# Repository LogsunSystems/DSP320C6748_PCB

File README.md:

### DSP320C6748 DSP DVK Board

The DVK board is based on the DSP chip from *Texas Instruments* DSP chip **DSP320C6748**. 

## Introduction
**DSP320C6748 DVK** is a scalable evaluation platform designed for high-performance applications requiring *real-time signal processing* and *embedded analytics*.

## Specifications
- **Processor:-** TSM320C6748 DSP with fixed and floating point core running at performance levels up to 456MHz
- **RAM:-**
- **Flash:-** 2Gbit, 16-bit Bus, Parallel Flash memory
- **Audio Coded:-**
- **Video Coded:-**
- **Connectivity:-**
- **Interfaces:-** 
    - Camera Connector
    - LCD Connector
    - RCA Video IN
    - Audio Line IN
    - MIC IN
    - Speaker IN (Mono)

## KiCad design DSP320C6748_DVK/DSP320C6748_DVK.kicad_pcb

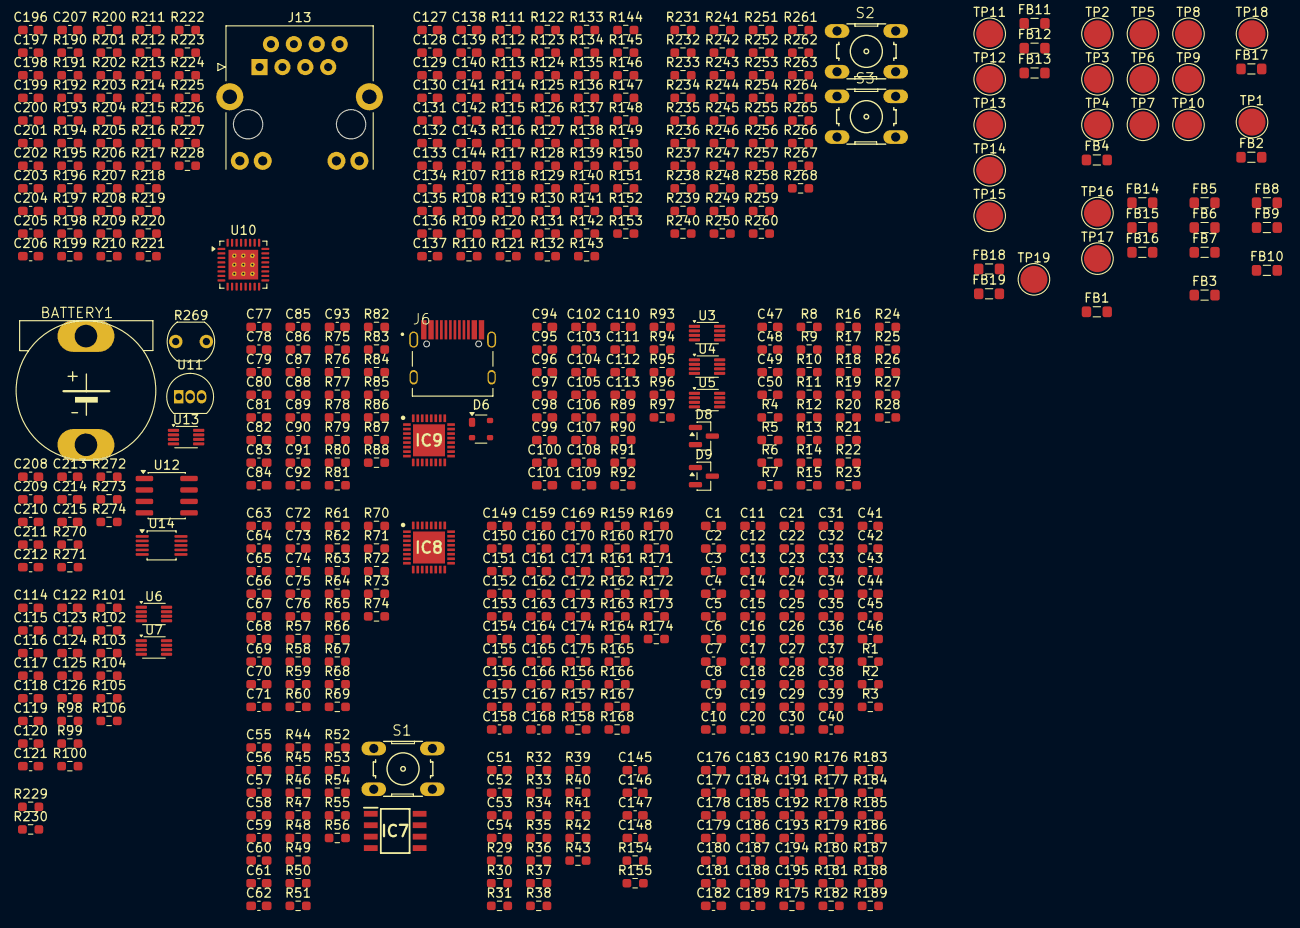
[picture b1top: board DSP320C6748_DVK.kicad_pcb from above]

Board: 8 copper layers, 549 parts (0 on the bottom side), 159 nets, no tracks yet.

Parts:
BATTERY1: LGS-KC-LEADED
C1, C2: 0.22uF/6.3V X5R; C_0603_1608Metric_Pad1.08x0.95mm_HandSolder
C3, C4, C5, C6, C7, C8, C9, C10, C11, C12, C13, C14, C15, C16, C17, C18, C19, C20, C21, C22, C23, C25, C26, C27, C28, C29, C30, C31, C32, C33, C34, C35, C36, C37, C39, C40, C41, C43, C47, C57, C58, C61, C62, C77, C78, C79, C81, C82, C91, C93, C94, C95, C96, C97, C98, C99, C102, C106, C112, C114, C115, C116, C117, C118, C119, C120, C121, C122, C123, C124, C125, C126, C127, C128, C130, C132, C134, C138, C139, C142, C145, C146, C149, C150, C151, C152, C153, C155, C156, C157, C158, C159, C160, C161, C162, C163, C164, C165, C166, C167, C168, C169, C170, C171, C172, C175, C176, C178, C180, C182, C185, C186, C187, C189, C192, C193, C195, C196, C202, C204, C210, C211, C212, C213, C215: 0.1uF/16V/X7R; C_0603_1608Metric_Pad1.08x0.95mm_HandSolder
C24, C38, C42, C44, C45, C46, C49, C55, C56, C59, C60, C63, C64, C65, C66, C67, C68, C69, C73, C75, C80, C83, C87, C88, C92, C113, C129, C137, C143, C188, C190, C191, C194, C206, C214: 10uF/10V/X5R; C_0603_1608Metric_Pad1.08x0.95mm_HandSolder
C48, C50, C173, C174: 22pF,50V NPO; C_0603_1608Metric_Pad1.08x0.95mm_HandSolder
C51, C52, C53, C54, C84, C85, C131, C133, C135, C136, C140, C141, C144, C147: 0.01uF/16V/X7R; C_0603_1608Metric_Pad1.08x0.95mm_HandSolder
C70, C71, C109, C148, C197: 1uF/10V/X5R; C_0603_1608Metric_Pad1.08x0.95mm_HandSolder
C72, C74, C76: 2.2uF/6.3V/X5R; C_0603_1608Metric_Pad1.08x0.95mm_HandSolder
C86: 10pF,50V NPO; C_0603_1608Metric_Pad1.08x0.95mm_HandSolder
C89: 4.7uF; C_0603_1608Metric_Pad1.08x0.95mm_HandSolder
C90: 0.1uF; C_0603_1608Metric_Pad1.08x0.95mm_HandSolder
C100, C104, C105: 100pF/25V; C_0603_1608Metric_Pad1.08x0.95mm_HandSolder
C101, C107, C108: 33pF/50V; C_0603_1608Metric_Pad1.08x0.95mm_HandSolder
C103, C110, C111: 270pF/50V; C_0603_1608Metric_Pad1.08x0.95mm_HandSolder
C154: 330pF/100V/X7R; C_0603_1608Metric_Pad1.08x0.95mm_HandSolder
C177: 1uF/16V/X7R; C_0603_1608Metric_Pad1.08x0.95mm_HandSolder
C179, C181: 220pF/50V X7R; C_0603_1608Metric_Pad1.08x0.95mm_HandSolder
C183, C184: 0.47uF/16V/X5R; C_0603_1608Metric_Pad1.08x0.95mm_HandSolder
C198, C199: 33pF,50V NPO; C_0603_1608Metric_Pad1.08x0.95mm_HandSolder
C200, C201, C203, C205: 10pF; C_0603_1608Metric_Pad1.08x0.95mm_HandSolder
C207: 0.022uF,50V; C_0603_1608Metric_Pad1.08x0.95mm_HandSolder
C208, C209: 12.5pF; C_0603_1608Metric_Pad1.08x0.95mm_HandSolder
D6: SP0503BAHT; SOT-143
D8, D9: BAV99; SOT-23
FB1, FB2, FB3, FB4, FB5, FB6, FB7, FB8, FB9, FB10, FB11, FB12, FB13, FB14, FB15, FB16, FB17, FB18, FB19: MMZ2012S121A; L_0805_2012Metric_Pad1.05x1.20mm_HandSolder
IC7: TPS3707-33DR; SOIC127P600X175-8N
IC8: TPS650250RHBR; QFN50P500X500X100-33N-D
IC9: CDCM61001RHBT; QFN50P500X500X100-33N-D
J6: USB_Type_C; LGS-KC-VALCON_CSP-USC16-TR
J13: RJ45_Halo_HFJ11-x2450E-LxxRL; RJ45_HALO_HFJ11-x2450E-LxxRL_Horizontal
R1: 0R, 5%, 1/10W; R_0603_1608Metric_Pad0.98x0.95mm_HandSolder
R2: 0R; R_0603_1608Metric_Pad0.98x0.95mm_HandSolder
R3: 49.9R, 1%, 1/16W; R_0603_1608Metric_Pad0.98x0.95mm_HandSolder
R4, R21, R36, R37, R38, R39: 100R,1%,1/16W; R_0603_1608Metric_Pad0.98x0.95mm_HandSolder
R5, R6, R11, R12, R22, R23, R24, R32, R33, R34, R35, R45, R82, R83, R91, R92, R93, R94, R95, R96, R97, R161, R261, R262: 10K,1%,1/16W; R_0603_1608Metric_Pad0.98x0.95mm_HandSolder
R7, R8, R9, R10, R13, R14, R16, R44, R49, R51, R53, R55, R56, R67, R70, R71, R72, R75, R76, R77, R78, R79, R80, R81, R98, R100, R101, R103, R105, R134, R154, R155, R157, R158, R162, R163, R164, R165, R166, R167, R168, R169, R170, R171, R172, R183, R192, R194, R204, R205, R207, R209, R210, R212, R213, R272, R273, R274: 4.7K,5%,1/16W; R_0603_1608Metric_Pad0.98x0.95mm_HandSolder
R15, R17, R89, R90: 2.2K,5%; R_0603_1608Metric_Pad0.98x0.95mm_HandSolder
R18, R19, R20, R109, R110, R119, R120, R130, R131, R132, R135, R136, R137, R138, R139: 22R,1%,1/16W; R_0603_1608Metric_Pad0.98x0.95mm_HandSolder
R25: 180R,1%; R_0603_1608Metric_Pad0.98x0.95mm_HandSolder
R26: 120R,1%; R_0603_1608Metric_Pad0.98x0.95mm_HandSolder
R27, R28, R31, R69, R74, R159, R175, R176, R214, R217, R218, R219, R220, R221, R222, R229, R230: 0R,5%,1/10W; R_0603_1608Metric_Pad0.98x0.95mm_HandSolder
R29, R30, R184: 33R,5%,1/16W; R_0603_1608Metric_Pad0.98x0.95mm_HandSolder
R40, R41, R265, R266: 100K,5%,1/16W; R_0603_1608Metric_Pad0.98x0.95mm_HandSolder
R42, R43, R227, R228, R267, R268: 330R,5%,1/16W; R_0603_1608Metric_Pad0.98x0.95mm_HandSolder
R46, R47: 5.1K; R_0603_1608Metric_Pad0.98x0.95mm_HandSolder
R48: 510R,5%,1/16W; R_0603_1608Metric_Pad0.98x0.95mm_HandSolder
R50, R231, R232, R233, R234, R239, R240, R241, R242, R243, R244, R253, R254, R255, R256, R257, R258, R259, R260, R263, R264: 1K.1%,1/16W; R_0603_1608Metric_Pad0.98x0.95mm_HandSolder
R52: 1K; R_0603_1608Metric_Pad0.98x0.95mm_HandSolder
R54, R107, R124: 1K,1%,1/16W; R_0603_1608Metric_Pad0.98x0.95mm_HandSolder
R57: 576K,1%,1/10W; R_0603_1608Metric_Pad0.98x0.95mm_HandSolder
R58: 60.4K,1%,1/16W; R_0603_1608Metric_Pad0.98x0.95mm_HandSolder
R59, R60, R61: 0.05R,1%,Sense; R_0603_1608Metric_Pad0.98x0.95mm_HandSolder
R62: 499K,1%,1/16W; R_0603_1608Metric_Pad0.98x0.95mm_HandSolder
R63: 300K,1%,1/16W; R_0603_1608Metric_Pad0.98x0.95mm_HandSolder
R64: 200K,1%,1/16W; R_0603_1608Metric_Pad0.98x0.95mm_HandSolder
R65: 160K,1%,1/10W; R_0603_1608Metric_Pad0.98x0.95mm_HandSolder
R66: 1R,1%,1/16W; R_0603_1608Metric_Pad0.98x0.95mm_HandSolder
R68: 1.4K,1%,1/16W; R_0603_1608Metric_Pad0.98x0.95mm_HandSolder
R73: 5.6K,1%,1/16W; R_0603_1608Metric_Pad0.98x0.95mm_HandSolder
R84: 22.1K,1%,1/4W; R_0603_1608Metric_Pad0.98x0.95mm_HandSolder
R85: 47.5K,1%,1/4W; R_0603_1608Metric_Pad0.98x0.95mm_HandSolder
R86: 1K,1%,1/4W; R_0603_1608Metric_Pad0.98x0.95mm_HandSolder
R87, R88, R173: 1K,5%,1/16W; R_0603_1608Metric_Pad0.98x0.95mm_HandSolder
R99: 3.4K,1%,1/16W; R_0603_1608Metric_Pad0.98x0.95mm_HandSolder
R102, R104, R106, R156: 75R,5%,1/16W; R_0603_1608Metric_Pad0.98x0.95mm_HandSolder
R108, R111, R112, R113, R114, R115, R116, R117, R118, R121, R122, R123, R125, R126, R127, R128, R129, R133, R140, R141, R142, R143, R144, R145, R146, R147, R148, R149, R150, R151, R152, R153, R208, R225: 10R,1%,1/16W; R_0603_1608Metric_Pad0.98x0.95mm_HandSolder
R160: 100K,5%; R_0603_1608Metric_Pad0.98x0.95mm_HandSolder
R174: 20K,5%,1/16W; R_0603_1608Metric_Pad0.98x0.95mm_HandSolder
R177, R180, R181, R182, R188, R189: 2K,1%,1,16W; R_0603_1608Metric_Pad0.98x0.95mm_HandSolder
R178, R179: 5.6K,1%; R_0603_1608Metric_Pad0.98x0.95mm_HandSolder
R185, R186: 20K,1%,1/16W; R_0603_1608Metric_Pad0.98x0.95mm_HandSolder
R187: 20K,5%; R_0603_1608Metric_Pad0.98x0.95mm_HandSolder
R190, R191: 1.5K,1%,1,16W; R_0603_1608Metric_Pad0.98x0.95mm_HandSolder
R193, R195, R196, R197, R198, R199, R200, R201, R202, R203: 100R,1%,1,16W; R_0603_1608Metric_Pad0.98x0.95mm_HandSolder
R206: 1M,1%,1/16%; R_0603_1608Metric_Pad0.98x0.95mm_HandSolder
R211: 12.1K,1%,1,16W; R_0603_1608Metric_Pad0.98x0.95mm_HandSolder
R215, R216, R223, R224: 49.9R,1%,1/16W; R_0603_1608Metric_Pad0.98x0.95mm_HandSolder
R226: 0R,5%,1210; R_0603_1608Metric_Pad0.98x0.95mm_HandSolder
R235, R236, R237, R238: 10K.1%,1/16W; R_0603_1608Metric_Pad0.98x0.95mm_HandSolder
R245, R246, R247, R248, R249, R250, R251, R252: 5.6K.1%,1/16W; R_0603_1608Metric_Pad0.98x0.95mm_HandSolder
R269: LDR07; R_LDR_5.1x4.3mm_P3.4mm_Vertical
R270: 10K; R_0603_1608Metric_Pad0.98x0.95mm_HandSolder
R271: 45K; R_0603_1608Metric_Pad0.98x0.95mm_HandSolder
S1, S2, S3: Tact_SW; LGS-KC-B3F-10XX
TP1, TP2, TP3, TP4, TP5, TP6, TP7, TP8, TP9, TP10, TP11, TP12, TP13, TP14, TP15, TP16, TP17, TP18, TP19: TestPoint_Alt; TestPoint_Pad_D3.0mm
U3, U6, U13: TXS0102DCU; VSSOP-8_2.3x2mm_P0.5mm
U4, U5, U7: SN74LVC2T45DCUR; VSSOP-8_2.3x2mm_P0.5mm
U10: LAN8710A; QFN-32-1EP_5x5mm_P0.5mm_EP3.3x3.3mm_ThermalVias
U11: LM35-LP; TO-92_Inline
U12: DS1307Z+; SOIC-8_3.9x4.9mm_P1.27mm
U14: ADS1115IDGS; TSSOP-10_3x3mm_P0.5mm

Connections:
5VD_IN: C59.1, C60.1, C61.1, R44.2, TP7.1 (1_1)
5V_{IN}: C55.1, C56.1, C57.1, R45.1
+1V3D: C8.1, C12.1, C16.1, C19.1, C23.1, C27.1, C30.1, C33.1, C37.1, C40.1, C44.1, C65.1, C68.1, R1.1, R2.1, R50.1, R61.1, TP5.1 (1_1)
+1V8D_Audio: C176.2, C177.2, FB14.1
+3V3ADAC: C106.1, C109.2, C114.1, FB8.2
+3V3A_ADC: C211.2, C213.2, C214.1, FB18.1, R269.1, R273.1, U11.1 (+V_{S}), U14.8 (VDD)
+3V3A_Audio: C192.2, C193.2, C194.1, FB16.1
+3V3A_Flash: C145.2, C146.2, C147.2, C148.2, FB10.2, R154.1, R155.1
+3V3A_LAN: C202.2, C204.2, C206.1, FB17.2, R215.2, R216.2, R223.2, R224.2, R225.1, U10.1 (VDD2A), U10.27 (VDD1A)
+3V3A_{SATA}: C77.1, C78.1, C79.1, C80.1, FB6.1, IC9.9 (VCC__VCO), IC9.16 (VCC__PLL2), IC9.18 (VCC__PLL1)
+3V3D_Audio: C180.2, C182.2, C185.2, C187.2, C188.1, FB15.1
/ADC_RTC/ADDR: R274.2, U14.1 (ADDR)
/ADC_RTC/ALERT/RDY: R273.2, U14.2 (ALERT/RDY)
/ADC_RTC/LDR: R269.2, R270.1
/ADC_RTC/SQW/OUT: R272.2, TP19.1 (1_1), U12.7 (SQW/OUT)
/ADC_RTC/VBAT: BATTERY1.P1 (+), U12.3 (VBAT)
/ADC_RTC/X1: C208.2, U12.1 (X1)
/ADC_RTC/X2: R271.2, U12.2 (X2)
/DSP-I/OSC_{IN}: R25.2, R26.1
/LAN_8710A/ACT_LED: R212.2, R227.1, U10.3 (LED1/~REGOFF)
/LAN_8710A/ENET_RXN: C203.1, J13.6 (RD-), R223.1, U10.30 (RXN)
/LAN_8710A/ENET_RXP: C205.1, J13.3 (RD+), R224.1, U10.31 (RXP)
/LAN_8710A/ENET_TXN: C200.1, J13.2 (TD-), R215.1, U10.28 (TXN)
/LAN_8710A/ENET_TXP: C201.1, J13.1 (TD+), R216.1, U10.29 (TXP)
/LAN_8710A/LINK_LED: J13.10, R213.2, U10.2 (LED2/~INTSEL)
/LAN_8710A/RXD2: R193.1, R210.1, U10.9 (RXD2/~RMIISEL)
/Power_Supply-I/~MR: IC7.1 (~MR), S1.1 (S), S1.2 (S1)
/Serial_SATA/CE: IC9.7 (CE), R83.1
/Serial_SATA/OD0: IC9.13 (OD0), R76.1
/Serial_SATA/OD1: IC9.14 (OD1), R79.1
/Serial_SATA/OD2: IC9.15 (OD2), R77.1
/Serial_SATA/OS0: IC9.11 (OS0), R75.1
/Serial_SATA/OS1: IC9.10 (OS1), R78.1
/Serial_SATA/OUTN: C85.1, IC9.5 (OUTN)
/Serial_SATA/OUTP: C84.1, IC9.6 (OUTP)
/Serial_SATA/PR0: IC9.25 (PR0), R81.1
/Serial_SATA/PR1: IC9.26 (PR1), R80.1
/Serial_SATA/REG_CAP1: C87.1, IC9.19 (REG_CAP1)
/Serial_SATA/REG_CAP2: C88.1, IC9.17 (REG_CAP2)
/Serial_SATA/USB_UART_DN: D6.3 (K), J6.A7 (DN1), J6.B7 (DN2)
/Serial_SATA/USB_UART_DP: D6.4 (K), J6.A6 (DP1), J6.B6 (DP2)
/Serial_SATA/USB_VBUS: C91.1, FB7.1, J6.A4 (VBUS_A), J6.A9 (VBUS_A), J6.B4 (VBUS_B), J6.B9 (VBUS_B)
/Serial_SATA/USB_VCC: C92.1, C93.1, D6.2 (K), FB7.2, R84.1
/Serial_SATA/VBUS: R84.2, R85.1
/Serial_SATA/VIO: C89.1, C90.1, R86.2
/Serial_SATA/XIN: C86.1, IC9.21 (XIN)
/Sound_Coded/Audio_Left: C191.2, R185.2
/Sound_Coded/Audio_Right: C190.2, R186.2
/Sound_Coded/MIC_BIAS: R177.2, R180.2
/Sound_Coded/MIC_DET: C184.2, R180.1
/Sound_Coded/SELECT: R188.1, R189.2
/Video_Decoder (page 12)/XTAL1: C173.1, R160.1
/Video_Decoder (page 12)/XTAL2: R159.2, R160.2
A18VDD_REF: C155.2, C158.2, FB12.2
ABPB: C100.1, C101.1, R106.1
AGND1: FB4.2, IC8.13 (AGND2), IC8.31 (AGND1), IC8.33 (EP)
AGY: C104.1, C107.1, R102.1
ARPR: C105.1, C108.1, R104.1
CH1_A33VDD: C166.2, C169.2, FB13.2
DDC_SCL: D9.3 (K), R90.2, U3.8 (B1)
DDC_SDA: D8.3 (K), R89.2, U3.1 (B2)
DEFDCDC1: C69.1, C70.1, C71.2, C73.1, C75.1, C96.2, C98.1, C210.1, D8.2 (A), D9.2 (A), IC8.4 (VINDCDC3), IC8.5 (VINDCDC1), IC8.9 (DEFDCDC1), IC8.15 (VINLDO), IC8.28 (VINDCDC2), R51.1, R52.1, R53.1, R55.1, R56.1, R66.1, R70.1, R71.1, R72.1, R73.1, R74.1, R89.1, R90.1, R267.1, R268.1, R272.1, TP3.1 (1_1), U3.7 (VCCB), U5.1 (VCCA), U12.8 (VCC), U13.3 (VCCA), U13.6 (OE)
DEFDCDC2: BATTERY1.P2 (-), C1.2, C2.2, C3.2, C4.2, C5.2, C6.2, C7.2, C8.2, C9.2, C10.2, C11.2, C12.2, C13.2, C14.2, C15.2, C16.2, C17.2, C18.2, C19.2, C20.2, C21.2, C22.2, C23.2, C24.2, C25.2, C26.2, C27.2, C28.2, C29.2, C30.2, C31.2, C32.2, C33.2, C34.2, C35.2, C36.2, C37.2, C38.2, C39.2, C40.2, C41.2, C42.2, C43.2, C44.2, C45.2, C46.2, C47.2, C49.2, C55.2, C56.2, C57.2, C58.2, C59.2, C60.2, C61.2, C62.1, C63.2, C64.2, C65.2, C66.2, C67.2, C68.2, C69.2, C70.2, C71.1, C72.2, C73.2, C74.2, C75.2, C76.2, C77.2, C78.2, C79.2, C80.2, C81.2, C82.2, C83.2, C86.2, C87.2, C88.2, C89.2, C90.2, C91.2, C92.2, C93.2, C94.2, C95.2, C96.1, C97.1, C98.2, C99.1, C102.2, C112.2, C113.2, C115.2, C116.2, C117.2, C118.2, C119.1, C120.1, C121.2, C122.1, C123.1, C124.1, C125.1, C126.1, C127.1, C129.1, C130.1, C131.1, C132.1, C133.1, C134.1, C135.1, C136.1, C137.1, C138.1, C139.1, C140.1, C141.1, C142.1, C143.1, C144.1, C145.1, C146.1, C147.1, C148.1, C149.1, C150.1, C151.1, C152.1, C153.1, C154.1, C155.1, C156.1, C157.1, C158.1, C159.1, C161.1, C162.1, C163.1, C164.1, C165.1, C166.1, C167.1, C168.1, C169.1, C170.1, C171.1, C172.1, C173.2, C174.2, C175.2, C176.1, C177.1, C179.1, C180.1, C181.1, C182.1, C185.1, C187.1, C188.2, C189.1, C192.1, C193.1, C194.2, C195.1, C196.2, C197.2, C198.1, C199.1, C200.2, C201.2, C202.1, C203.2, C204.1, C205.2, C206.2, C207.2, C208.1, C209.1, C210.2, C212.1, C215.1, D6.1 (A), FB2.2, FB3.2, FB4.1, FB5.1, FB9.1, FB19.1, IC7.3 (GND), IC8.2 (PGND3), IC8.7 (PGND1), IC8.22 (DEFDCDC2), IC8.26 (PGND2), IC9.22 (GND1), IC9.33 (GND), J6.A1 (GND_A), J6.A12 (GND_A), J6.B1 (GND_B), J6.B12 (GND_B), J13.8, J13.12, R3.1, R13.2, R15.2, R17.2, R23.1, R26.2, R40.2, R41.2, R44.1, R46.1, R47.1, R49.1, R62.2, R63.2, R64.2, R67.2, R68.2, R69.2, R78.2, R79.2, R80.2, R81.2, R83.2, R85.2, R99.2, R102.2, R103.2, R104.2, R105.2, R106.2, R107.1, R134.1, R156.2, R157.2, R158.2, R161.1, R164.2, R178.2, R179.2, R181.2, R182.2, R185.1, R186.1, R187.1, R189.1, R210.2, R211.2, R212.1, R226.1, R229.2, R230.2, R231.2, R232.2, R233.2, R234.2, R242.1, R243.1, R244.1, R253.2, R254.2, R255.2, R256.2, R257.2, R258.2, R259.2, R260.2, R263.2, R264.2, R265.2, R266.2, S1.3, S1.4 (P1), TP2.1 (1_1), TP6.1 (1_1), U3.2 (GND), U4.4 (GND), U4.5 (DIR), U5.4 (GND), U5.5 (DIR), U6.2 (GND), U7.4 (GND), U7.5 (DIR), U10.33 (VSS), U12.4 (GND), U13.2 (GND)
DEFDCDC3: IC8.32 (DEFDCDC3), R57.1, R62.1
EMU_{0}: R16.2, R17.1
EMU_{1}: R14.2, R15.1
EN_DCDC1: IC8.20 (EN_DCDC1), R56.2
EN_DCDC2: IC8.19 (EN_DCDC2), R53.2
EN_DCDC3: IC8.18 (EN_DCDC3), R71.2
EN_LDO: IC8.17 (EN_LDO), R70.2
FB_LDO1: IC8.11 (FB_LDO1), R58.2, R63.1
FB_LDO2: IC8.10 (FB_LDO2), R64.1, R65.2
GLCO/I2CA: R163.2, R164.1
GNDD: FB2.1, FB3.1, FB5.2, FB9.2, J6.S1 (SHELL_GND), J6.S2 (SHELL_GND), J6.S3 (SHELL_GND), J6.S4 (SHELL_GND)
GND_ADC: C211.1, C213.1, C214.2, FB19.2, R270.2, R274.1, U11.3 (GND), U14.3 (GND)
GPIO2[4]: R261.2, S2.3, S2.4 (P1)
GPIO2[5]: R262.2, S3.3, S3.4 (P1)
GPIO6[9]: R241.1, R244.2
GPIO6[10]: R240.1, R243.2
GPIO6[11]: R239.1, R242.2
I2C_{0}_SCL: R32.1, R173.2, U3.5 (A1), U6.8 (B1), U13.8 (B1), U14.10 (SCL)
I2C_{0}_SDA: R33.1, R174.2, U3.4 (A2), U6.1 (B2), U13.1 (B2), U14.9 (SDA)
IOVDD_1: C3.1, C5.1, C7.1, C11.1, C15.1, C18.1, C22.1, C26.1, C29.1, C32.1, C36.1, C39.1, C43.1, C46.1, C47.1, C62.2, C63.1, C66.1, C81.1, C82.1, C83.1, C94.1, C97.2, C99.2, C102.1, C112.1, C113.1, C119.2, C120.2, C124.2, C125.2, C126.2, C163.2, C164.2, C165.2, C168.2, C175.1, C189.2, C195.2, C196.1, C212.2, C215.2, FB6.2, FB8.1, FB10.1, FB13.1, FB15.2, FB16.2, FB17.1, FB18.2, IC7.2 (VDD), IC9.4 (VCC__OUT), IC9.20 (VCC__IN), R5.2, R6.2, R7.2, R8.2, R9.2, R10.2, R11.2, R12.2, R14.1, R16.1, R21.2, R22.2, R24.1, R32.2, R33.2, R34.2, R35.2, R42.1, R43.1, R59.1, R75.2, R76.2, R77.2, R82.2, R91.1, R92.1, R93.1, R94.1, R95.1, R96.1, R97.1, R162.1, R163.1, R165.2, R166.2, R167.2, R168.2, R169.2, R170.2, R171.2, R172.2, R173.1, R174.1, R183.2, R188.2, R190.2, R191.2, R192.1, R194.1, R204.1, R205.1, R207.1, R209.1, R213.1, R228.1, R235.2, R236.2, R237.2, R238.2, R239.2, R240.2, R241.2, R245.2, R246.2, R247.2, R248.2, R249.2, R250.2, R251.2, R252.2, R261.1, R262.1, TP4.1 (1_1), U3.3 (VCCA), U3.6 (OE), U4.8 (VCCB), U5.8 (VCCB), U6.7 (VCCB), U7.8 (VCCB), U10.12 (VDDIO), U13.7 (VCCB)
LCD_AC_ENB_~CS_1V8: R98.2, U4.3 (A2)
LCD_BLUE: C101.2, C103.1
LCD_GREEN: C107.2, C110.1
LCD_HSYNC: U5.7 (B1), U7.7 (B1)
LCD_RED: C108.2, C111.1
LCD_VSYNC: U5.6 (B2), U7.6 (B2)
MIDO_CLK: R191.1, U10.17 (MDC)
MIDO_D: R190.1, U10.16 (MDIO)
MII_COL: R202.2, R209.2
MII_CRS: R203.2, R217.2
MII_RXCLK: R200.2, R205.2, R219.2
MII_RXDV: R199.2, R220.2
MII_RXD[0]: R192.2, R196.2
MII_RXD[1]: R194.2, R197.2
MII_RXD[2]: R193.2, R221.2
MII_RXD[3]: R198.2, R204.2, R222.2
MII_RXER: R201.2, R207.2, R218.2
MII_TXD_{0}: R38.1, U10.22 (TXD0)
MII_TXD_{1}: R36.1, U10.23 (TXD1)
MII_TXD_{2}: R39.1, U10.24 (TXD2)
MII_TXD_{3}: R37.1, U10.25 (TXD3)
MODE: IC8.23 (MODE), R69.1, R74.2
unnamed: C154.2, C160.1, FB11.2, R156.1
unnamed: C174.1, R159.1
unnamed: C178.2, C179.2, R176.1, R178.1
unnamed: C181.2, C186.2, R175.1, R179.1
unnamed: C183.2, R177.1
unnamed: C198.2, R208.2
unnamed: C209.2, R271.1
unnamed: IC8.24 (EN_VDD_ALIVE), R67.1
unnamed: IC8.29 (VCC), R66.2
unnamed: J13.9, R228.2
unnamed: J13.11, R227.2
unnamed: J13.SH, R226.2
unnamed: C207.1, J13.4 (TCT), J13.5 (RCT), R225.2
unnamed: R4.2, TP1.1 (1_1)
unnamed: R263.1, S2.1 (S), S2.2 (S1)
unnamed: R264.1, S3.1 (S), S3.2 (S1)
unnamed: C49.1, R27.2
unnamed: R202.1, U10.15 (COL/CRS_DV/~MODE2)
unnamed: R203.1, U10.14 (CRS)
unnamed: R211.1, U10.32 (RBIAS)
unnamed: R200.1, U10.7 (RXCLK/~PHYAD1)
unnamed: R196.1, U10.11 (RXD0/~MODE0)
unnamed: R197.1, U10.10 (RXD1/~MODE1)
unnamed: R198.1, U10.8 (RXD3/~PHYAD2)
unnamed: R199.1, U10.26 (RXDV)
unnamed: R201.1, U10.13 (RXER/RXD4/~PHYAD0)
unnamed: R195.1, U10.20 (TXCLK)
unnamed: C197.1, TP18.1 (1_1), U10.6 (VDDCR)
unnamed: R206.1, R208.1, U10.5 (XTAL1/CLKIN)
unnamed: C199.2, R206.2, U10.4 (XTAL2)
unnamed: R214.2, U10.18 (~INT/TXER/TXD4)
PWRFAIL_SNS: IC8.30 (PWRFAIL_SNS), R68.1, R73.2
RTC_SCL: U12.6 (SCL), U13.5 (A1)
RTC_SDA: U12.5 (SDA), U13.4 (A2)
RTC_VSS: C48.2, C50.2
TCK: R6.1, R20.2
UART_{2}_RXD: R34.1, R88.1
UART_{2}_TXD: R35.1, R87.1
USB_{0}_~DRVBUS: R22.1, R23.2
VBUS_{0}_K: C58.1, R49.2
VDAC_AGND: C100.2, C103.2, C104.2, C105.2, C106.2, C109.1, C110.2, C111.2, D8.1 (K), D9.1 (K)
VDCDC3: IC8.1 (VDCDC3), R57.2
VDDL: C4.1, C6.1, C10.1, C13.1, C17.1, C21.1, C25.1, C28.1, C31.1, C34.1, C38.1, C42.1, C45.1, C64.1, C67.1, C95.1, C115.1, C117.1, C118.1, C121.1, C122.2, C123.2, C128.2, C129.2, C130.2, C131.2, C132.2, C133.2, C134.2, C135.2, C136.2, C137.2, C138.2, C139.2, C140.2, C141.2, C142.2, C143.2, C144.2, C151.2, C167.2, C170.2, C171.2, C172.2, FB12.1, FB14.2, R54.1, R60.1, R98.1, R100.1, R101.1, R124.2, TP8.1 (1_1), U4.1 (VCCA), U6.3 (VCCA), U6.6 (OE), U7.1 (VCCA)
VDD_ALIVE: C76.1, IC8.12 (VDD_ALIVE), TP9.1 (1_1)
VLDO1: C9.1, C14.1, C20.1, C24.1, C74.1, FB1.1, IC8.16 (VLDO1), R58.1
VLDO2: C35.1, C41.1, C72.1, IC8.14 (VLDO2), R65.1
VPIF_DOUT_{8}: R234.1, R238.1
VPIF_DOUT_{13}: R233.1, R237.1
VPIF_DOUT_{14}: R232.1, R236.1
VPIF_DOUT_{15}: R231.1, R235.1
VREF_DDR: C127.2, C128.1, R107.2, R124.1
~FLAG: R45.2, R48.2
~PHP_RST: IC9.12 (~RSTN), R82.1, U10.19 (~RST)
~PWRFAIL: IC8.21 (~PWRFAIL), R72.2, TP10.1 (1_1)

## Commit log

2026-03-28 Prefoundational Structure made
2026-03-28 Kicad Project Created
2026-04-02 .gitignore modified
2026-04-03 Power section schematic Partially completed
2026-04-04 gitignore updated
2026-04-04 TPS650250 Section Added
2026-04-04 POR Generation Section Added
2026-04-04 Partial Serial Circuit Added
2026-04-04 Serial Circuit completed, SATA section Added, DSP Reset Section Added
2026-04-05 LCDK schematic added for referencce
2026-04-05 gitignore modified
2026-04-05 Partial VGA-LCD schematic added
2026-04-06 LCD Schematic Completed
2026-04-06 DDR_RAM and Video Decoder Schematic Added
2026-04-06 Video and Audio Codec Schematic added
2026-04-07 LAN Schematic Added
2026-04-07 Connectors and mislleneous components added
2026-04-08 NAND Flash circuit and Power Testpoints added
2026-04-08 Whole Schematic Reannotation Done
2026-04-08 Schematic PDF Exported
2026-04-08 README updated
2026-04-08 Schematic corrections-I
2026-04-09 Schematic Corrections-II Done
2026-04-09 SATA Connector Added
2026-04-09 Re-Annotation done
2026-04-09 Updated Scheamtic exported to PDF
2026-04-10 DC jack Replaced With Type-C, ADC and RTC section added
2026-04-10 Scheamtic Re-annotation done, Some footprints assigned
2026-04-10 Updated Schematic exported to PDF
